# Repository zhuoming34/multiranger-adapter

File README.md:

# multiranger-adapter

## **NOTE**
Traces are not drawn in a good way, say, should be 90 degrees. Please redraw them in your manner

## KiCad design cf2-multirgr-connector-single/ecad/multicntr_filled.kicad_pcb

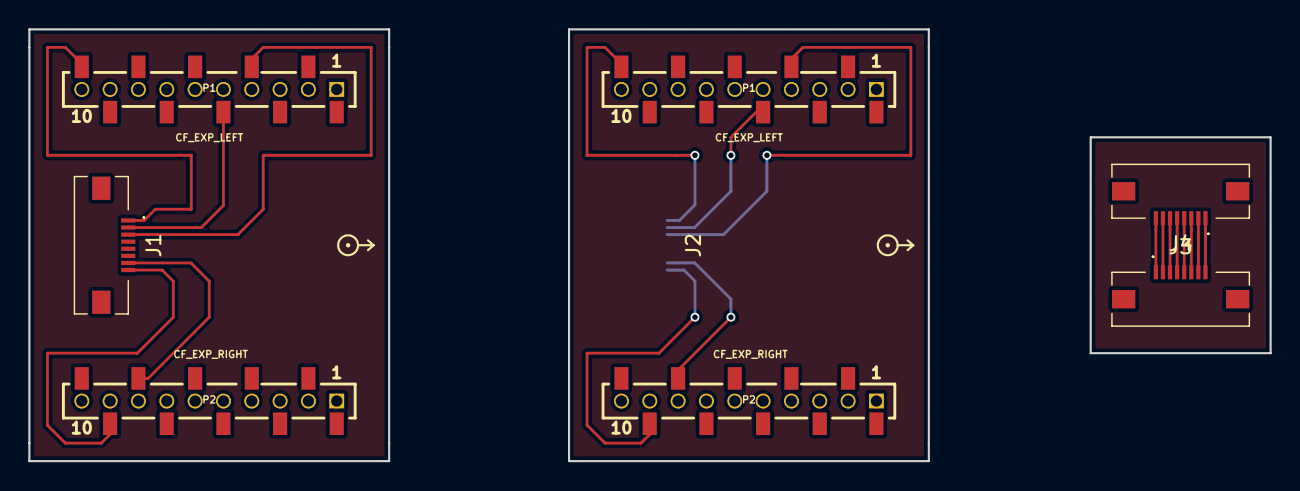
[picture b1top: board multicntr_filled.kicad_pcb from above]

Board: 2 copper layers, 87.6 x 30.5 mm, 10 parts (1 on the bottom side), 13 nets.

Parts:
EXP_ORIENTATION: VAL**; EXP_ORIENTATION
EXP_ORIENTATION#2: VAL**; EXP_ORIENTATION
J1, J2, J3, J4: Conn_01x08; 687108183722
P1, P1#2: CF_EXP_LEFT; BF090-10-X-B2
P2, P2#2: CF_EXP_RIGHT; BF090-10-X-B2

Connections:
unnamed: J1.1, P1#2.10
unnamed: J1.2, P1#2.5
unnamed: J1.3, P1#2.4
unnamed: J1.7, P2#2.8
unnamed: J1.8, P2#2.9
unnamed: J3.1, J4.8
unnamed: J3.2, J4.7
unnamed: J3.3, J4.6
unnamed: J3.4, J4.5
unnamed: J3.5, J4.4
unnamed: J3.6, J4.3
unnamed: J3.7, J4.2
unnamed: J3.8, J4.1

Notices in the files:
cf2-multirgr-connector-single/ecad/multicntr_filled.kicad_pcb:
Licensed under CC-BY 4.0
